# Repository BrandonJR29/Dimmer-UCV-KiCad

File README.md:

<!DOCTYPE html>
<html lang="en">
<head>
  <title>Dimmer with Kicad</title>
  <meta charset="UTF-8">
</head>
  
<body>
<h1> Dimmer-KiCad </h1>

<header>
This is a design in KiCad of a Dimmer.
</header>

<div id="pcb-soldermask" align="center">
  <h2> PCB soldermask</h2>
  
</div>

<div id="pcb" align="center">
  <h2>PCB</h2>
  
</div>
</body>

</html>

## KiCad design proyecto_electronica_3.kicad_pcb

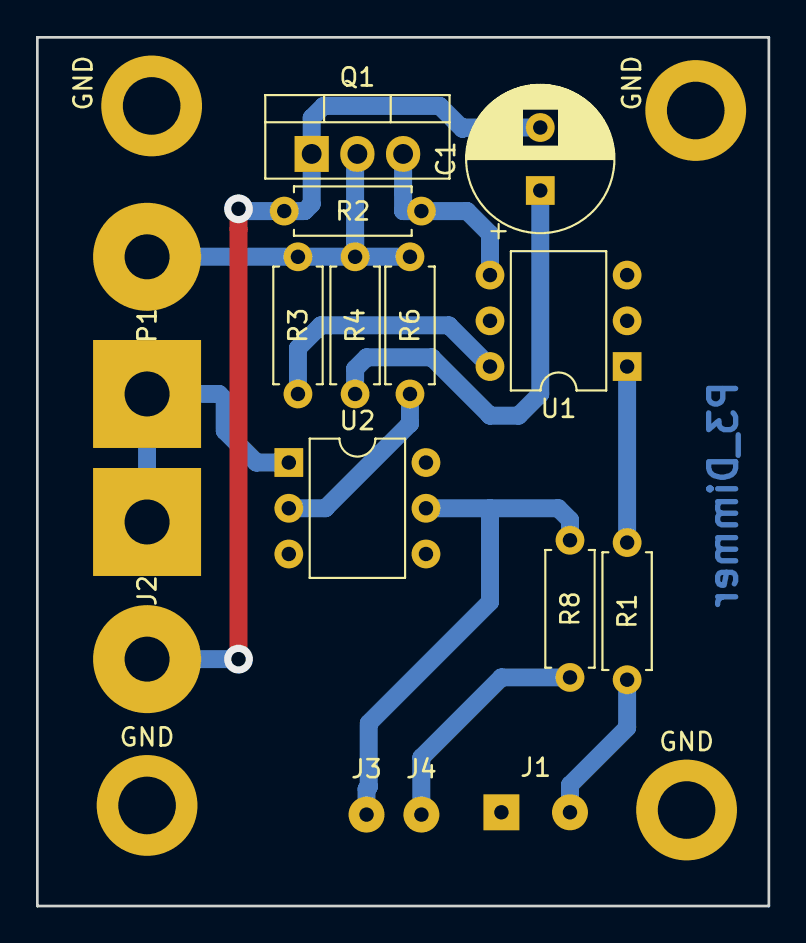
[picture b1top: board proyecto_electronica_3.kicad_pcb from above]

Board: 2 copper layers, 40.6 x 48.3 mm, 19 parts (0 on the bottom side), 12 nets.

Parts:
C1: CP; CP_Radial_D8.0mm_P3.50mm
GND: MountingHole_3.2mm_M3_DIN965_Pad
GND#2, GND#3, GND#4: MountingHole_3.2mm_M3_DIN965_Pad
J1: out_micro; SolderWirePad_1x02_P3.81mm_Drill0.8mm
J2: carga; SolderWirePad_1x02_P7.62mm_Drill2.5mm
J3: input_micro; SolderWirePad_1x01_Drill0.8mm
J4: 5V; SolderWirePad_1x01_Drill0.8mm
P1: source 120V; SolderWirePad_1x02_P7.62mm_Drill2.5mm
Q1: BT136-500; TO-220-3_Vertical
R1, R2, R3, R4, R6, R8: R; R_Axial_DIN0207_L6.3mm_D2.5mm_P7.62mm_Horizontal
U1: MOC3021M; DIP-6_W7.62mm
U2: 4N37; DIP-6_W7.62mm

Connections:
GND: GND.1, GND#2.1, GND#3.1, GND#4.1, J1.1, U1.2, U2.4
unnamed: C1.1, R4.2
unnamed: C1.2, J2.2, Q1.1, R2.2
unnamed: J1.2, R1.2
unnamed: J2.1, P1.1, U2.1
unnamed: J3.1, R8.1, U2.5
unnamed: J4.1, R8.2
unnamed: P1.2, Q1.2, R3.1, R4.1, R6.1
unnamed: Q1.3, R2.1, U1.4
unnamed: R1.1, U1.1
unnamed: R3.2, U1.6
unnamed: R6.2, U2.2

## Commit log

2019-04-19 Dimmer project first commit
